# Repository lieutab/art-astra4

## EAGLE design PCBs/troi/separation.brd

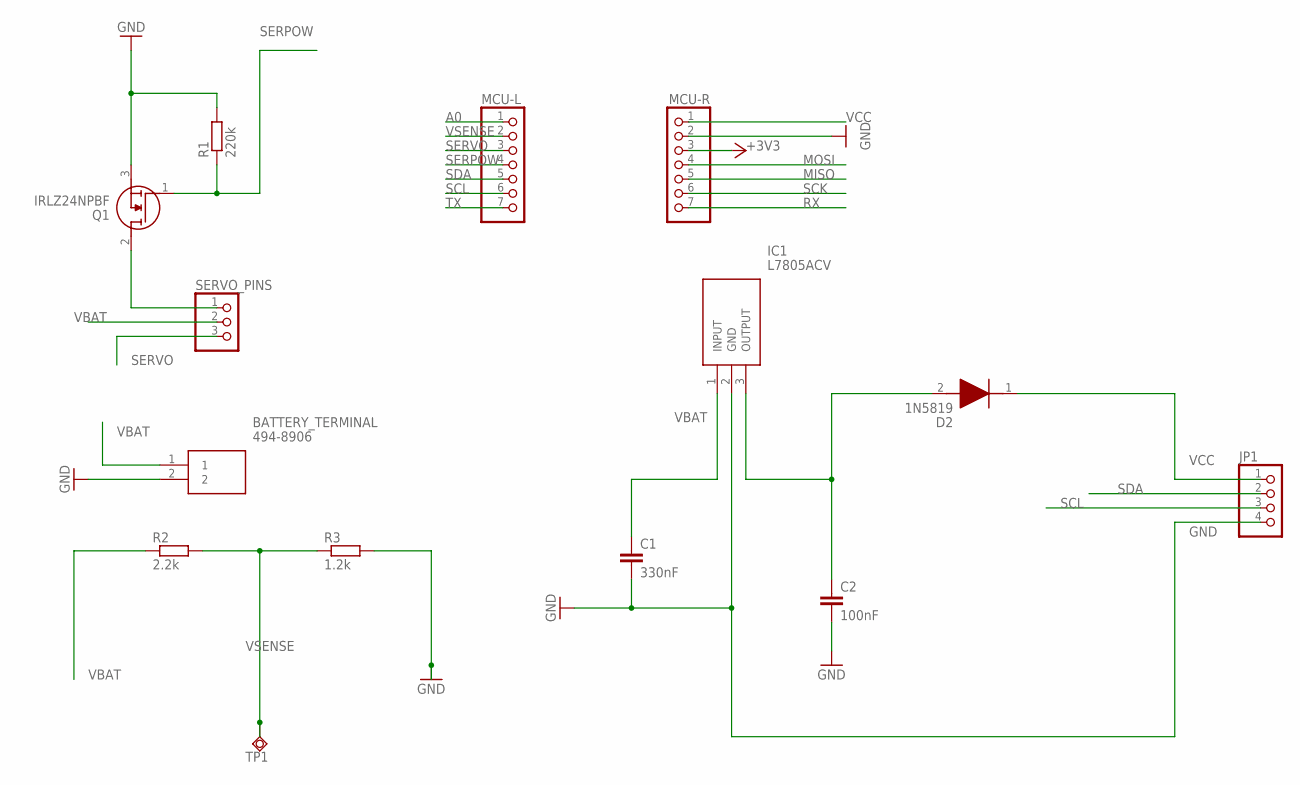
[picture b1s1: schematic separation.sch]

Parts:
BATTERY_TERMINAL: 494-8906; SHDR2W100P0X500_1X2_1000X750X1
C1: 330nF; C2.5-3
C2: 100nF; C2.5-3
D2: 1N5819; DIOAD1414W86L464D238
IC1: L7805ACV; TO255P460X1020X2008-3P
JP1: PINHD-1X4; 1X04
MCU-L: PINHD-1X7; 1X07
MCU-R: PINHD-1X7; 1X07
Q1: IRLZ24NPBF; TO254P469X1042X1967-3P
R1: 220k; 0204/7
R2: 2.2k; 0204/7
R3: 1.2k; 0204/7
SERVO_PINS: PINHD-1X3; 1X03
TP1: TPSQB1,27; B1,27

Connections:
+3V3: MCU-R.3
A0: MCU-L.1
GND: BATTERY_TERMINAL.2, C1.2, C2.2, IC1.2 (GND), JP1.4, MCU-R.2, Q1.3 (S), R1.2, R3.2
MISO: MCU-R.5
MOSI: MCU-R.4
unnamed: Q1.2 (D), SERVO_PINS.1
unnamed: C2.1, D2.2 (A), IC1.3 (OUTPUT)
RX: MCU-R.7
SCK: MCU-R.6
SCL: JP1.3, MCU-L.6
SDA: JP1.2, MCU-L.5
SERPOW: MCU-L.4, Q1.1 (G), R1.1
SERVO: MCU-L.3, SERVO_PINS.3
TX: MCU-L.7
VBAT: BATTERY_TERMINAL.1, C1.1, IC1.1 (INPUT), R2.1, SERVO_PINS.2
VCC: D2.1 (K), JP1.1, MCU-R.1
VSENSE: MCU-L.2, R2.2, R3.1, TP1.TP

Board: 2 copper layers, 14 parts (0 on the bottom side), 10 nets, no tracks yet.

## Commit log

2023-02-11 added MCU
2023-02-11 added servo connection
2023-02-11 Added library
2023-02-11 battery
2023-02-11 added battery terminal
2023-02-11 added mosfet transistor
2023-02-11 Added MOSIFET
2023-02-14 complete rest of separation schematic
2023-02-14 placing components
2023-02-21 21-Feb-2023
    changes to the board
2023-02-25 Troi Value Changes
    Just changed the value of the resistors in the potentiometer (potential divider).
2023-02-28 separation board arrangement
2023-03-07 Create separation.b##
2023-03-21 Apogee
